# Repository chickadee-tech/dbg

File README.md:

# Chickadee Tech Debug Polystack Mod #
This mod breaks out all connections in the Polystack connector. It can either be used in place of a **control** board or within a polystack.

## Documentation ##
See the [wiki](https://github.com/chickadee-tech/dbg/wiki) for documentation.

## Polystack ##
This **mod** board is part of the Polystack platform for modular microcontrol systems. More information on the platform can be found at [polystack.org](http://polystack.org).

## Support ##
If you need support with a board you own or have development questions please email support@chickadee.tech or check [chickadee.tech/support](https://chickadee.tech/support) for other ways to get support.

## Contributing ##
Please note that this project is released with a [Contributor Code of Conduct](CODE_OF_CONDUCT.md). By participating in this project you agree to abide by its terms.

### Setup ###
Components and footprints for PCB parts are not included in this repository. Instead, checkout the [chickadee-tech/kicad-libs](https://github.com/chickadee-tech/kicad-libs) repository in the same directory that this repository is checked out in. All part definitions should be relative so that they will load correctly.

### Pull requests ###
For fixes please submit a pull request to the original repository. After the pull request is merged, check the [Chickadee Tech Active Contributor Discount (ACD)](https://chickadee.tech/active-contributor) to see if you are eligible for a discount code to use on your next purchase.

### Derivatives ###
If developing your own version of the Debug board please remove all Chickadee Tech trademarks and follow the [CC-BY license](LICENSE). While not required, please consider open sourcing your modifications so others can learn from your improvements. If you do email support@chickadee.tech and we may choose to add your project to the ACD.

You may also license the Polystack logo for free by emailing support@chickadee.tech. We'll ask for your gerbers to ensure the design complies with specifications laid out [here](https://github.com/chickadee-tech/polystack/wiki) and provide written permission to use the trademark after compliance has been demonstrated.

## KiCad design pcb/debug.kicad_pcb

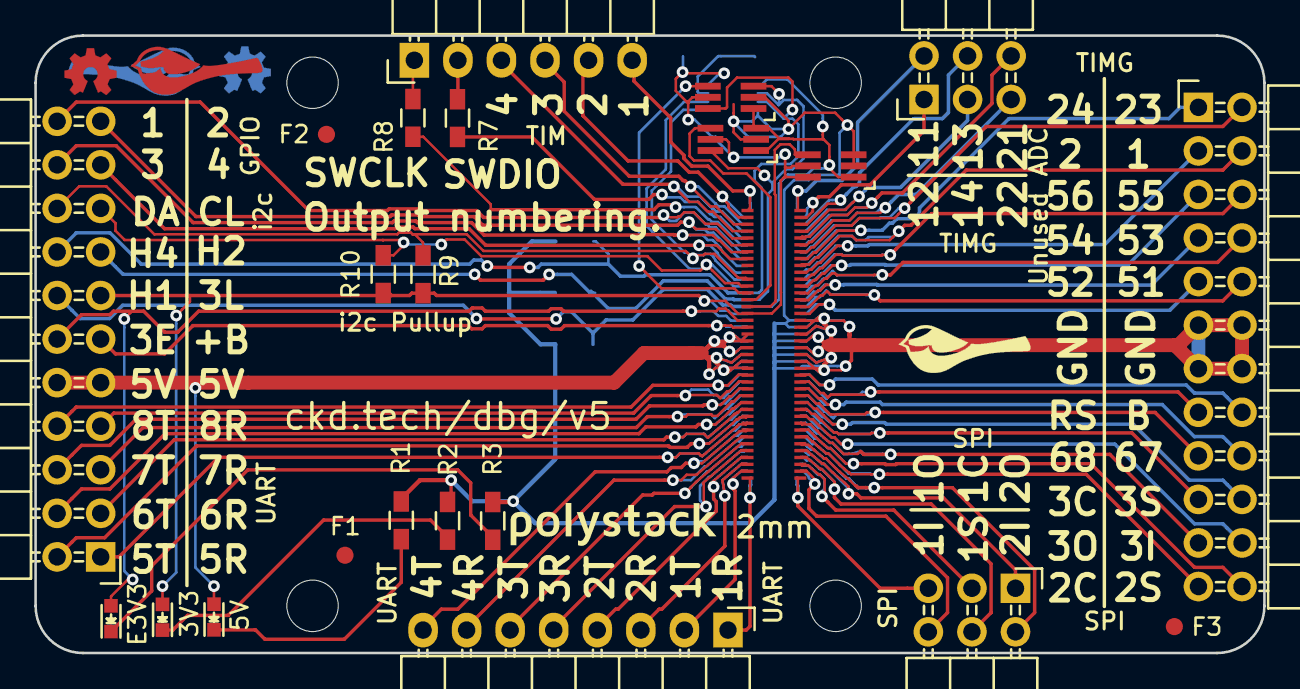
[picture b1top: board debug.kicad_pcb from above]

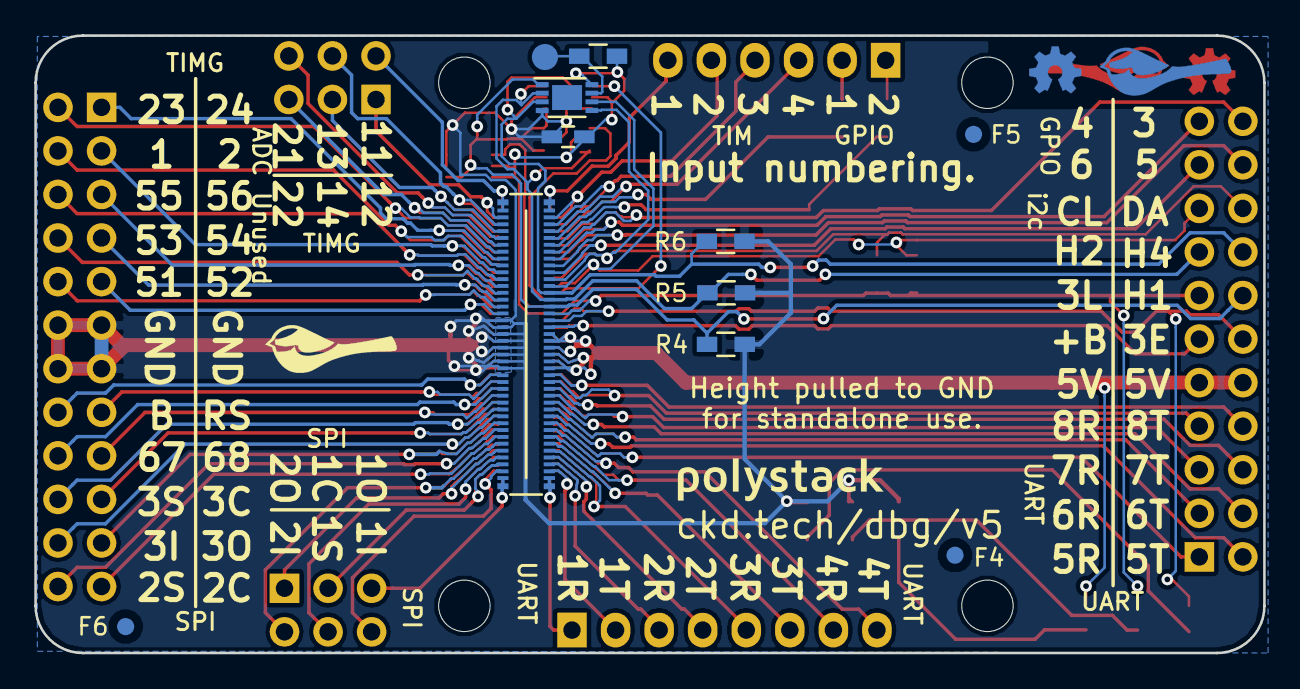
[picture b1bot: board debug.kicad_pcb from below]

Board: 2 copper layers, 71.7 x 36.0 mm, 36 parts (12 on the bottom side), 77 nets.

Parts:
D1: Green; LED-0603
D2: Yellow; LED-0603
D3: Red; LED-0603
F1, F2, F3, F4, F5, F6: 1mm; Fiducial
P1: CONN_01X06; Pin_Header_Angled_1x06
P2: CONN_02X11; Pin_Header_Angled_2x11
P3: CONN_01X08; Pin_Header_Angled_1x08
P4, P6: CONN_02X03; Pin_Header_Angled_2x03
P5: CONN_02X12; Pin_Header_Angled_2x12
PORT_ANDOR1: SN74LVC1G0832; SC-70-6_Handsoldering
PORT_C1: 0.1uF; C_0603_HandSoldering
PORT_IC1: AT24CS02-MAHM; DFN-8-1EP_3x2mm_Pitch0.5mm
PORT_IN1: CKD_SANDWICH; DF40-80pin-Header
PORT_INV1: SN74LVC1G58; SC-70-6_Handsoldering
PORT_OUT1: CKD_SANDWICH; DF40-3-4mm-80pin-Receptacle
PORT_P1: CONN_01X01; Measurement_Point_Round-SMD-Pad_Small
PORT_R1: 10k; R_0603_HandSoldering
PORT_XOR1: SN74LVC1G58; SC-70-6_Handsoldering
R1, R2, R3: 1k; R_0603_HandSoldering
R4, R5, R6, R9, R10: 10k; R_0603_HandSoldering
R7, R8: 470; R_0603_HandSoldering
svg2mod, svg2mod#2: G***; polystack-bold-0.625

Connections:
+5V: D1.2, P2.9, P2.10, PORT_IN1.19, PORT_IN1.20, PORT_IN1.21, PORT_IN1.22, PORT_IN1.23, PORT_IN1.24, PORT_OUT1.19, PORT_OUT1.20, PORT_OUT1.21, PORT_OUT1.22, PORT_OUT1.23, PORT_OUT1.24
/ExpansionPort/3V3_0.3A_E: D3.2, P2.12, PORT_IN1.17, PORT_OUT1.17
/ExpansionPort/3V3_0.3A_LL: D2.2, P2.13, PORT_ANDOR1.5, PORT_C1.1, PORT_IC1.8, PORT_IN1.16, PORT_INV1.5, PORT_INV1.6, PORT_OUT1.16, PORT_R1.2, PORT_XOR1.5, R9.1, R10.1
/ExpansionPort/+BATT: P2.11, PORT_IN1.18, PORT_OUT1.18
/ExpansionPort/ADC1: P5.4, PORT_IN1.49, PORT_OUT1.49
/ExpansionPort/ADC2: P5.3, PORT_IN1.50, PORT_OUT1.50
/ExpansionPort/BOOT: P5.16, PORT_IN1.65, PORT_OUT1.65
/ExpansionPort/CAN_HI: P5.18, PORT_IN1.67, PORT_OUT1.67
/ExpansionPort/CAN_LO: P5.17, PORT_IN1.68, PORT_OUT1.68
/ExpansionPort/GPIO1: PORT_IN1.5, R7.2
/ExpansionPort/GPIO2: PORT_IN1.6, R8.2
/ExpansionPort/GPIO3: P2.22, PORT_IN1.7, PORT_OUT1.5
/ExpansionPort/GPIO4: P2.21, PORT_IN1.8, PORT_OUT1.6
/ExpansionPort/GPIO5: P2.20, PORT_IN1.9, PORT_OUT1.7
/ExpansionPort/GPIO6: P2.19, PORT_IN1.10, PORT_OUT1.8
/ExpansionPort/HEIGHT_1: P2.14, PORT_ANDOR1.1, PORT_IC1.1, PORT_IN1.15, PORT_INV1.1, PORT_XOR1.1, PORT_XOR1.3, R4.1
/ExpansionPort/HEIGHT_2: P2.15, PORT_ANDOR1.3, PORT_IC1.2, PORT_IN1.14, PORT_XOR1.6, R5.1
/ExpansionPort/HEIGHT_4: P2.16, PORT_ANDOR1.6, PORT_IC1.3, PORT_IN1.13, R6.1
/ExpansionPort/NEW_HEIGHT_1: PORT_INV1.4, PORT_OUT1.15
/ExpansionPort/NEW_HEIGHT_2: PORT_OUT1.14, PORT_XOR1.4
/ExpansionPort/NEW_HEIGHT_4: PORT_ANDOR1.4, PORT_OUT1.13
/ExpansionPort/RESET: P5.15, PORT_IN1.66, PORT_OUT1.66
/ExpansionPort/SDMMC1_CK: P5.10, PORT_IN1.55, PORT_OUT1.55
/ExpansionPort/SDMMC1_CMD: P5.9, PORT_IN1.56, PORT_OUT1.56
/ExpansionPort/SDMMC1_D0: P5.6, PORT_IN1.51, PORT_OUT1.51
/ExpansionPort/SDMMC1_D1: P5.5, PORT_IN1.52, PORT_OUT1.52
/ExpansionPort/SDMMC1_D2: P5.8, PORT_IN1.53, PORT_OUT1.53
/ExpansionPort/SDMMC1_D3: P5.7, PORT_IN1.54, PORT_OUT1.54
/ExpansionPort/SPI1_MISO: P6.6, PORT_IN1.79, PORT_OUT1.79
/ExpansionPort/SPI1_MOSI: P6.5, PORT_IN1.80, PORT_OUT1.80
/ExpansionPort/SPI1_NSS: P6.4, PORT_IN1.77, PORT_OUT1.77
/ExpansionPort/SPI1_SCK: P6.3, PORT_IN1.78, PORT_OUT1.78
/ExpansionPort/SPI2_MISO: P6.2, PORT_IN1.75, PORT_OUT1.75
/ExpansionPort/SPI2_MOSI: P6.1, PORT_IN1.76, PORT_OUT1.76
/ExpansionPort/SPI2_NSS: P5.24, PORT_IN1.73, PORT_OUT1.73
/ExpansionPort/SPI2_SCK: P5.23, PORT_IN1.74, PORT_OUT1.74
/ExpansionPort/SPI3_MISO: P5.22, PORT_IN1.71, PORT_OUT1.71
/ExpansionPort/SPI3_MOSI: P5.21, PORT_IN1.72, PORT_OUT1.72
/ExpansionPort/SPI3_NSS: P5.20, PORT_IN1.69, PORT_OUT1.69
/ExpansionPort/SPI3_SCK: P5.19, PORT_IN1.70, PORT_OUT1.70
/ExpansionPort/TIM1: P1.6, PORT_IN1.1, PORT_OUT1.1
/ExpansionPort/TIM2: P1.5, PORT_IN1.2, PORT_OUT1.2
/ExpansionPort/TIM3: P1.4, PORT_IN1.3, PORT_OUT1.3
/ExpansionPort/TIM4: P1.3, PORT_IN1.4, PORT_OUT1.4
/ExpansionPort/TIMG1_CH1: P4.2, PORT_IN1.41, PORT_OUT1.41
/ExpansionPort/TIMG1_CH2: P4.1, PORT_IN1.42, PORT_OUT1.42
/ExpansionPort/TIMG1_CH3: P4.4, PORT_IN1.43, PORT_OUT1.43
/ExpansionPort/TIMG1_CH4: P4.3, PORT_IN1.44, PORT_OUT1.44
/ExpansionPort/TIMG2_CH1: P4.6, PORT_IN1.45, PORT_OUT1.45
/ExpansionPort/TIMG2_CH2: P4.5, PORT_IN1.46, PORT_OUT1.46
/ExpansionPort/TIMG2_CH3: P5.2, PORT_IN1.47, PORT_OUT1.47
/ExpansionPort/TIMG2_CH4: P5.1, PORT_IN1.48, PORT_OUT1.48
/ExpansionPort/UART1_RX: P3.1, PORT_IN1.40, PORT_OUT1.40
/ExpansionPort/UART1_TX: P3.2, PORT_IN1.39, PORT_OUT1.39
/ExpansionPort/UART2_RX: P3.3, PORT_IN1.38, PORT_OUT1.38
/ExpansionPort/UART2_TX: P3.4, PORT_IN1.37, PORT_OUT1.37
/ExpansionPort/UART3_RX: P3.5, PORT_IN1.36, PORT_OUT1.36
/ExpansionPort/UART3_TX: P3.6, PORT_IN1.35, PORT_OUT1.35
/ExpansionPort/UART4_RX: P3.7, PORT_IN1.34, PORT_OUT1.34
/ExpansionPort/UART4_TX: P3.8, PORT_IN1.33, PORT_OUT1.33
/ExpansionPort/UART5_RX: P2.1, PORT_IN1.32, PORT_OUT1.32
/ExpansionPort/UART5_TX: P2.2, PORT_IN1.31, PORT_OUT1.31
/ExpansionPort/UART6_RX: P2.3, PORT_IN1.30, PORT_OUT1.30
/ExpansionPort/UART6_TX: P2.4, PORT_IN1.29, PORT_OUT1.29
/ExpansionPort/UART7_RX: P2.5, PORT_IN1.28, PORT_OUT1.28
/ExpansionPort/UART7_TX: P2.6, PORT_IN1.27, PORT_OUT1.27
/ExpansionPort/UART8_RX: P2.7, PORT_IN1.26, PORT_OUT1.26
/ExpansionPort/UART8_TX: P2.8, PORT_IN1.25, PORT_OUT1.25
/ExpansionPort/i2c_SCL: P2.17, PORT_IC1.6, PORT_IN1.12, PORT_OUT1.12, R10.2
/ExpansionPort/i2c_SDA: P2.18, PORT_IC1.5, PORT_IN1.11, PORT_OUT1.11, R9.2
GNDPWR: P5.11, P5.12, P5.13, P5.14, PORT_ANDOR1.2, PORT_C1.2, PORT_IC1.4, PORT_IN1.57, PORT_IN1.58, PORT_IN1.59, PORT_IN1.60, PORT_IN1.61, PORT_IN1.62, PORT_IN1.63, PORT_IN1.64, PORT_INV1.2, PORT_INV1.3, PORT_OUT1.57, PORT_OUT1.58, PORT_OUT1.59, PORT_OUT1.60, PORT_OUT1.61, PORT_OUT1.62, PORT_OUT1.63, PORT_OUT1.64, PORT_XOR1.2, R1.2, R2.2, R3.2, R4.2, R5.2, R6.2
unnamed: D1.1, R1.1
unnamed: D2.1, R2.1
unnamed: D3.1, R3.1
unnamed: P1.1, R8.1
unnamed: P1.2, R7.1
unnamed: PORT_IC1.7, PORT_P1.1, PORT_R1.1

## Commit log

2015-11-27 Debug board for chickadee v1.
2016-01-07 Debug v2 with pin function labels and add inline resistors for SWD lines.
2016-04-07 More logos and i2c label.
2016-04-13 Rebrand everything to Polystack and increment versions.
2016-04-16 Final gerbers for test manufacturing run.
2016-06-07 Update polystack logo to bold variant and bump version number.
2016-07-07 Add license information to many files. PCB design files are CC-BY and code is MIT license.
2016-07-07 Add back .gitignore after repo split.
2016-07-07 Convert to relative component and footprint paths.

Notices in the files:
pcb/debug.kicad_pcb:
Copyright 2016 Chickadee Tech LLC,
This work is licensed under the Creative Commons Attribution 4.0 International License.
To view a copy of this license, visit http://creativecommons.org/licenses/by/4.0
or send a letter to Creative Commons, PO Box 1866, Mountain View, CA 94042, USA.
